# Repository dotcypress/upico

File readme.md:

## μPico

### What is it?

uPico is a [RP2040](https://www.raspberrypi.com/products/rp2040/) powered expansion card designed to enhance the capabilities of [Clockwork's uConsole](https://www.clockworkpi.com/uconsole).

⚠️ Only R-01 and CM4 core are supported by control application.
Work in progress for A04/A06 core modules.

Second project name is `atto`, cause 10<sup>−6</sup> * 10<sup>-12</sup> = 10<sup>-18</sup> 🤓

### Features

* Internal Speakers Support
* Type-C (USB 2.0) port with programmable power switch and overcurrent protection
* 3.3V and 5V external power out with programmable switch and overcurrent protection
* RP2040 with extenal double-double PMOD compatible connector
* RP2040 controllable LED

## Resources

- [Schematics](docs/upico.pdf)
- [PCB Viewer](https://kicanvas.org/?github=https%3A%2F%2Fgithub.com%2Fdotcypress%2Fupico%2Fblob%2Fmain%2Fpcb%2Fupico.kicad_pcb)
- [Interactive BOM](https://htmlpreview.github.io/?https://github.com/dotcypress/upico/blob/main/docs/ibom.html)

### Control app installation

1. Download latest build from [Releases page](https://github.com/dotcypress/upico/releases)
2. Extract installer: `mkdir dist && tar -xzf upico_%version%.%core%.tar.gz -C dist`
3. Install: `cd dist && sudo ./install.sh`
4. Cleanup: `cd .. && rm -rf dist`
5. Print help: `upico help`

### Building control app from sources

1. Install rustup by following the instructions at https://rustup.rs
2. Clone this repo: `git clone git@github.com:dotcypress/upico.git && cd upico`
3. Build: `cargo build --release`
4. Install app: `sudo cp target/release/upico /usr/local/bin/`
5. Install service: `sudo cp upico.service /etc/systemd/system/`
6. Enable service: `sudo systemctl enable upico`
7. Start service: `sudo systemctl start upico`
8. Setup uPico extender USB device: `echo 'SUBSYSTEM=="usb",ATTRS{idVendor}=="1209",ATTRS{idProduct}=="bc07",MODE="0660",GROUP="plugdev"' > /etc/udev/rules.d/50-upico-permissions.rules`
9. Reload udev: `udevadm control --reload-rules`
10. Print help: `upico help`

### Flash firmware

1. `wget https://rptl.io/pico-blink`
2. `upico install pico-blink` or `upico install -m pico-blink` if automount is disabled for hot-plug devices.

See other examples: https://github.com/raspberrypi/pico-examples

### High level design diagram

### GPIO Header Pinout
```
╔══════╦══════╗
║ AUX  ║ AUX  ║
╠══════╬══════╣
║ VDD  ║ VDD  ║
║ GND  ║ GND  ║
║ IO3  ║ IO7  ║
║ IO2  ║ IO6  ║
║ IO1  ║ IO5  ║
║ IO0  ║ IO4  ║
╠══════╬══════╣
║ IO27 ║ IO29 ║
║ IO26 ║ IO28 ║
║ IO18 ║ IO19 ║
╠══════╬══════╣
║ VDD  ║ VDD  ║
║ GND  ║ GND  ║
║ IO11 ║ IO15 ║
║ IO10 ║ IO14 ║
║ IO9  ║ IO13 ║
║ IO8  ║ IO12 ║
╚══════╩══════╝
```

## Errata

### CM4 core & uPico PCB rev:0x02

* Overcurrent reporting feature isn't supported.

## License

Licensed under either of

- Apache License, Version 2.0 ([LICENSE-APACHE](LICENSE-APACHE) or
  http://www.apache.org/licenses/LICENSE-2.0)
- MIT license ([LICENSE-MIT](LICENSE-MIT) or http://opensource.org/licenses/MIT)

at your option.

### Contribution

Unless you explicitly state otherwise, any contribution intentionally submitted
for inclusion in the work by you, as defined in the Apache-2.0 license, shall be
dual licensed as above, without any additional terms or conditions.

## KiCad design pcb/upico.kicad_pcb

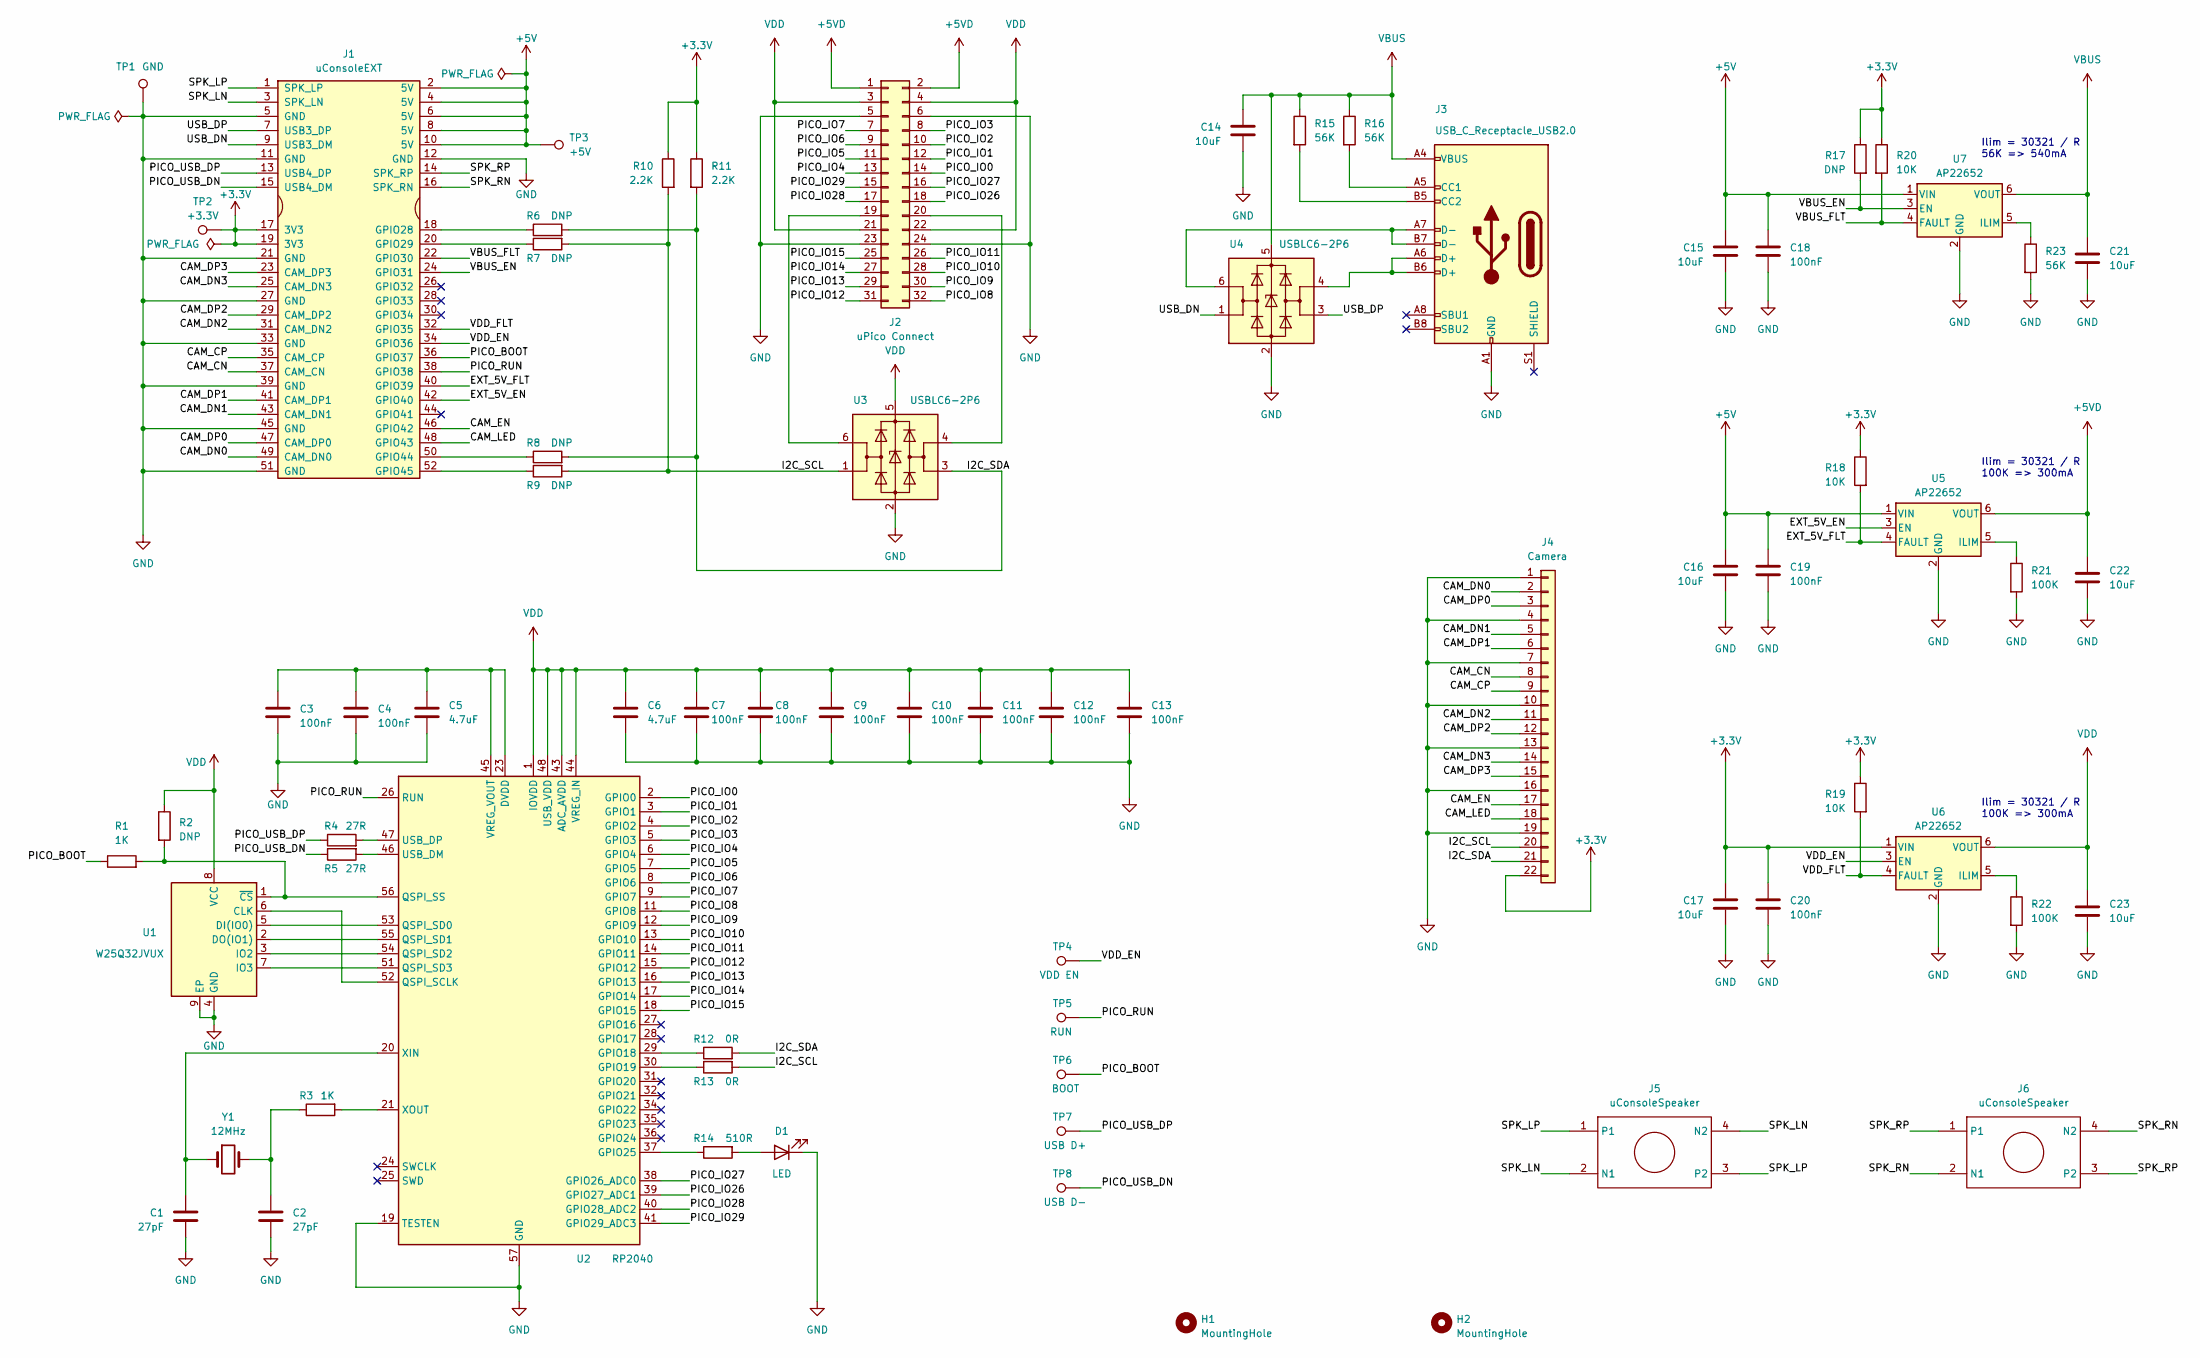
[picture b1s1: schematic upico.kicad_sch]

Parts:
C1, C2: 27pF; C_0402_1005Metric
C3, C4, C7, C8, C9, C10, C11, C12, C13, C18, C19, C20: 100nF; C_0402_1005Metric
C5, C6: 4.7uF; C_0402_1005Metric
C14, C15, C16, C17, C21, C22, C23: 10uF; C_0603_1608Metric
D1: LED; LED_SideEmitter_Rectangular_W4.5mm_H1.6mm
H1, H2: MountingHole; MountingHole_5.3mm_M5
J1: uConsoleEXT; ext
J2: uPico Connect; PinSocket_2x16_P2.54mm_Horizontal
J3: USB_C_Receptacle_USB2.0; USB_C_Receptacle_HRO_TYPE-C-31-M-12
J4: Camera; Hirose_FH12-22S-0.5SH_1x22-1MP_P0.50mm_Horizontal
J5, J6: uConsoleSpeaker; speaker
R1, R3: 1K; R_0402_1005Metric
R2, R6, R7, R8, R9, R17: DNP; R_0402_1005Metric
R4, R5: 27R; R_0402_1005Metric
R10, R11: 2.2K; R_0402_1005Metric
R12, R13: 0R; R_0402_1005Metric
R14: 510R; R_0402_1005Metric
R15, R16, R23: 56K; R_0402_1005Metric
R18, R19, R20: 10K; R_0402_1005Metric
R21, R22: 100K; R_0402_1005Metric
TP1: GND; TestPoint_Pad_D1.0mm
TP2: +3.3V; TestPoint_Pad_D1.0mm
TP3: +5V; TestPoint_Pad_D1.0mm
TP4: VDD EN; TestPoint_Pad_D1.0mm
TP5: RUN; TestPoint_Pad_D1.0mm
TP6: BOOT; TestPoint_Pad_D1.0mm
TP7: USB D+; TestPoint_Pad_D1.0mm
TP8: USB D-; TestPoint_Pad_D1.0mm
U1: W25Q32JVUX; USON-8_2x3mm_P0.5mm
U2: RP2040; QFN-56-1EP_7x7mm_P0.4mm_EP3.2x3.2mm
U3, U4: USBLC6-2P6; SOT-666
U5, U6, U7: AP22652; SOT-23-6
Y1: 12MHz; Crystal_SMD_5032-2Pin_5.0x3.2mm

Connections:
+3.3V: C17.2, C20.2, J1.17 (3V3), J1.19 (3V3), J4.22, R10.1, R11.1, R17.1, R18.1, R19.1, R20.1, TP2.1, U6.1 (VIN)
+5V: C15.2, C16.2, C18.2, C19.2, J1.2 (5V), J1.4 (5V), J1.6 (5V), J1.8 (5V), J1.10 (5V), TP3.1, U5.1 (VIN), U7.1 (VIN)
+5VD: C22.1, J2.1, J2.2, U5.6 (VOUT)
/CAM_CN: J1.37 (CAM_CN), J4.8
/CAM_CP: J1.35 (CAM_CP), J4.9
/CAM_DN0: J1.49 (CAM_DN0), J4.2
/CAM_DN1: J1.43 (CAM_DN1), J4.5
/CAM_DN2: J1.31 (CAM_DN2), J4.11
/CAM_DN3: J1.25 (CAM_DN3), J4.14
/CAM_DP0: J1.47 (CAM_DP0), J4.3
/CAM_DP1: J1.41 (CAM_DP1), J4.6
/CAM_DP2: J1.29 (CAM_DP2), J4.12
/CAM_DP3: J1.23 (CAM_DP3), J4.15
/CAM_EN: J1.46 (GPIO42), J4.17
/CAM_LED: J1.48 (GPIO43), J4.18
/EXT_5V_EN: J1.42 (GPIO40), U5.3 (EN)
/EXT_5V_FLT: J1.40 (GPIO39), R18.2, U5.4 (FAULT)
/I2C_SCL: J4.20, R7.2, R9.2, R10.2, R13.2, U3.1 (I/O1)
/I2C_SDA: J4.21, R6.2, R8.2, R11.2, R12.2, U3.3 (I/O2)
/PICO_BOOT: J1.36 (GPIO37), R1.1, TP6.1
/PICO_IO0: J2.14, U2.2 (GPIO0)
/PICO_IO1: J2.12, U2.3 (GPIO1)
/PICO_IO2: J2.10, U2.4 (GPIO2)
/PICO_IO3: J2.8, U2.5 (GPIO3)
/PICO_IO4: J2.13, U2.6 (GPIO4)
/PICO_IO5: J2.11, U2.7 (GPIO5)
/PICO_IO6: J2.9, U2.8 (GPIO6)
/PICO_IO7: J2.7, U2.9 (GPIO7)
/PICO_IO8: J2.32, U2.11 (GPIO8)
/PICO_IO9: J2.30, U2.12 (GPIO9)
/PICO_IO10: J2.28, U2.13 (GPIO10)
/PICO_IO11: J2.26, U2.14 (GPIO11)
/PICO_IO12: J2.31, U2.15 (GPIO12)
/PICO_IO13: J2.29, U2.16 (GPIO13)
/PICO_IO14: J2.27, U2.17 (GPIO14)
/PICO_IO15: J2.25, U2.18 (GPIO15)
/PICO_IO26: J2.18, U2.39 (GPIO27_ADC1)
/PICO_IO27: J2.16, U2.38 (GPIO26_ADC0)
/PICO_IO28: J2.17, U2.40 (GPIO28_ADC2)
/PICO_IO29: J2.15, U2.41 (GPIO29_ADC3)
/PICO_RUN: J1.38 (GPIO38), TP5.1, U2.26 (RUN)
/PICO_USB_DN: J1.15 (USB4_DM), R5.1, TP8.1
/PICO_USB_DP: J1.13 (USB4_DP), R4.1, TP7.1
/SPK_LN: J1.3 (SPK_LN), J5.2 (N1), J5.4 (N2)
/SPK_LP: J1.1 (SPK_LP), J5.1, J5.3 (P2)
/SPK_RN: J1.16 (SPK_RN), J6.2 (N1), J6.4 (N2)
/SPK_RP: J1.14 (SPK_RP), J6.1, J6.3 (P2)
/USB_DN: J1.9 (USB3_DM), U4.1 (I/O1)
/USB_DP: J1.7 (USB3_DP), U4.3 (I/O2)
/VBUS_EN: J1.24 (GPIO31), R17.2, U7.3 (EN)
/VBUS_FLT: J1.22 (GPIO30), R20.2, U7.4 (FAULT)
/VDD_EN: J1.34 (GPIO36), TP4.1, U6.3 (EN)
/VDD_FLT: J1.32 (GPIO35), R19.2, U6.4 (FAULT)
GND: C1.2, C2.2, C3.2, C4.2, C5.2, C6.2, C7.2, C8.2, C9.2, C10.2, C11.2, C12.2, C13.2, C14.1, C15.1, C16.1, C17.1, C18.1, C19.1, C20.1, C21.2, C22.2, C23.2, D1.1 (K), J1.5 (GND), J1.11 (GND), J1.12 (GND), J1.21 (GND), J1.27 (GND), J1.33 (GND), J1.39 (GND), J1.45 (GND), J1.51 (GND), J2.5, J2.6, J2.23, J2.24, J3.A1 (GND), J3.A12 (GND), J3.B1 (GND), J3.B12 (GND), J4.1, J4.4, J4.7, J4.10, J4.13, J4.16, J4.19, R21.2, R22.2, R23.2, TP1.1, U1.4 (GND), U1.9 (EP), U2.19 (TESTEN), U2.57 (GND), U3.2 (GND), U4.2 (GND), U5.2 (GND), U6.2 (GND), U7.2 (GND)
unnamed: C2.1, R3.1, Y1.2
unnamed: D1.2 (A), R14.2
unnamed: J1.18 (GPIO28), R6.1
unnamed: J1.20 (GPIO29), R7.1
unnamed: J1.50 (GPIO44), R8.1
unnamed: J1.52 (GPIO45), R9.1
unnamed: J2.19, U3.6 (I/O1)
unnamed: J2.20, U3.4 (I/O2)
unnamed: J3.A5 (CC1), R16.2
unnamed: J3.B5 (CC2), R15.2
unnamed: J3.A6 (D+), J3.B6 (D+), U4.4 (I/O2)
unnamed: J3.A7 (D-), J3.B7 (D-), U4.6 (I/O1)
unnamed: U1.6 (CLK), U2.52 (QSPI_SCLK)
unnamed: U1.5 (DI(IO0)), U2.53 (QSPI_SD0)
unnamed: U1.2 (DO(IO1)), U2.55 (QSPI_SD1)
unnamed: U1.3 (IO2), U2.54 (QSPI_SD2)
unnamed: U1.7 (IO3), U2.51 (QSPI_SD3)
unnamed: R1.2, R2.2, U1.1 (~CS), U2.56 (QSPI_SS)
unnamed: R12.1, U2.29 (GPIO18)
unnamed: R13.1, U2.30 (GPIO19)
unnamed: R14.1, U2.37 (GPIO25)
unnamed: R5.2, U2.46 (USB_DM)
unnamed: R4.2, U2.47 (USB_DP)
unnamed: C3.1, C4.1, C5.1, U2.23 (DVDD), U2.45 (VREG_VOUT), U2.50 (DVDD)
unnamed: C1.1, U2.20 (XIN), Y1.1
unnamed: R3.2, U2.21 (XOUT)
unnamed: R21.1, U5.5 (ILIM)
unnamed: R22.1, U6.5 (ILIM)
unnamed: R23.1, U7.5 (ILIM)
VBUS: C14.2, C21.1, J3.A4 (VBUS), J3.A9 (VBUS), J3.B4 (VBUS), J3.B9 (VBUS), R15.1, R16.1, U4.5 (VBUS), U7.6 (VOUT)
VDD: C6.1, C7.1, C8.1, C9.1, C10.1, C11.1, C12.1, C13.1, C23.1, J2.3, J2.4, J2.21, J2.22, R2.1, U1.8 (VCC), U2.1 (IOVDD), U2.10 (IOVDD), U2.22 (IOVDD), U2.33 (IOVDD), U2.42 (IOVDD), U2.43 (ADC_AVDD), U2.44 (VREG_IN), U2.48 (USB_VDD), U2.49 (IOVDD), U3.5 (VBUS), U6.6 (VOUT)

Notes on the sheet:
Ilim = 30321 / R 56K => 540mA
Ilim = 30321 / R 100K => 300mA

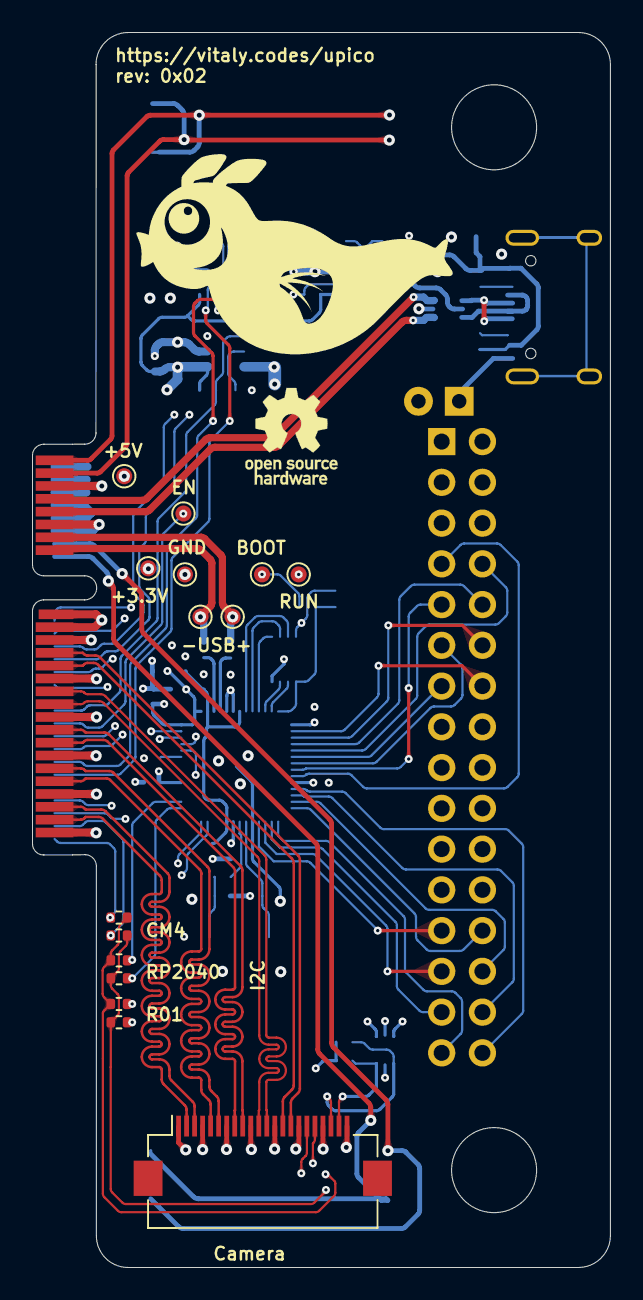
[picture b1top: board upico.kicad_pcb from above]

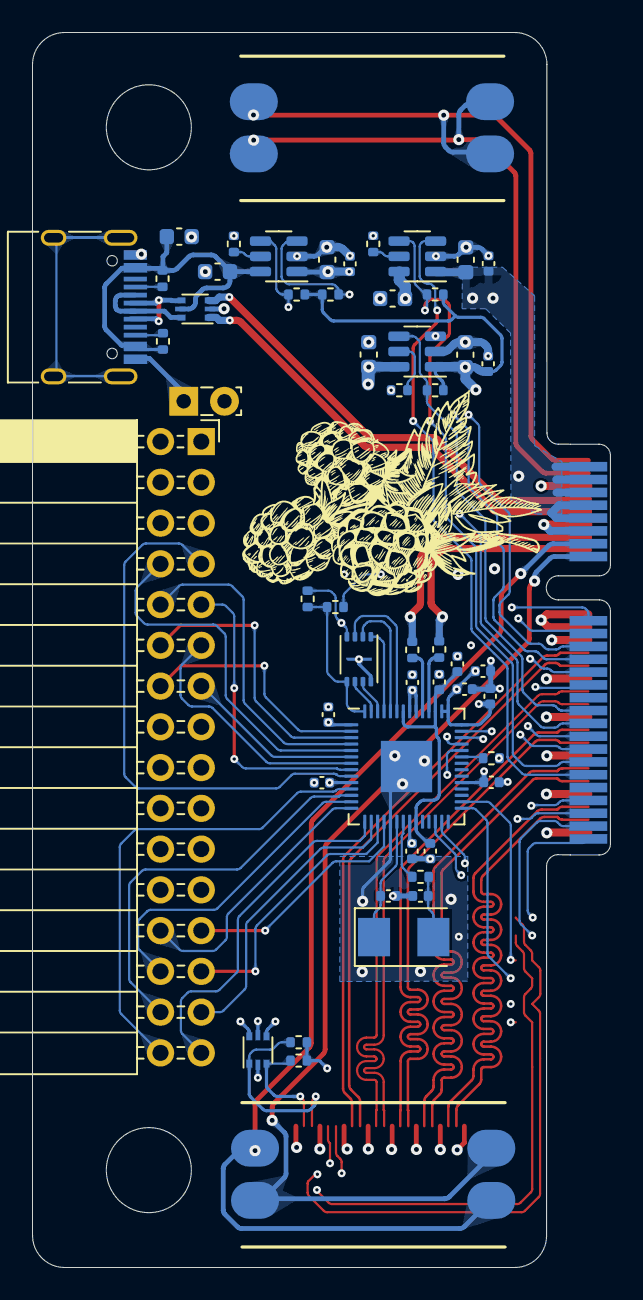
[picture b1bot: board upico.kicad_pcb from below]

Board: 6 copper layers, 36.0 x 77.0 mm, 71 parts (53 on the bottom side), 85 nets.

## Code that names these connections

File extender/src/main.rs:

#![no_std]
#![no_main]

extern crate panic_probe;
extern crate rp2040_hal as hal;
extern crate rtic;

use defmt_rtt as _;

mod upico;

use cortex_m::singleton;
use hal::adc;
use hal::gpio::*;
use hal::pac;
use hal::pio::{PIOBuilder, PIOExt};
use hal::timer::{monotonic::Monotonic, *};
use hal::usb::UsbBus;
use pio::Assembler;
use upico::*;
use usb_device::class_prelude::*;
use usb_device::prelude::*;

#[link_section = ".boot2"]
#[no_mangle]
#[used]
pub static BOOT2: [u8; 256] = rp2040_boot2::BOOT_LOADER_GENERIC_03H;

pub const XTAL_FREQ_HZ: u32 = 12_000_000_u32;

#[rtic::app(device = pac, peripherals = true, dispatchers = [SW0_IRQ, SW1_IRQ])]
mod app {
    use super::*;

    #[monotonic(binds = TIMER_IRQ_0, default = true)]
    type Oracle = Monotonic<Alarm0>;

    #[local]
    struct Local {
        upico: UpicoClass,
        usb_dev: UsbDevice<'static, hal::usb::UsbBus>,
    }

    #[shared]
    struct Shared {}

    #[init]
    fn init(ctx: init::Context) -> (Shared, Local, init::Monotonics) {
        let mut resets = ctx.device.RESETS;
        let mut watchdog = hal::Watchdog::new(ctx.device.WATCHDOG);
        let clocks = hal::clocks::init_clocks_and_plls(
            XTAL_FREQ_HZ,
            ctx.device.XOSC,
            ctx.device.CLOCKS,
            ctx.device.PLL_SYS,
            ctx.device.PLL_USB,
            &mut resets,
            &mut watchdog,
        )
        .ok()
        .expect("Clocks init failed");

        let mut timer = hal::Timer::new(ctx.device.TIMER, &mut resets, &clocks);
        let alarm = timer.alarm_0().expect("Alarm0 init failed");
        let mono = Monotonic::new(timer, alarm);

        let sio = hal::Sio::new(ctx.device.SIO);
        let pins = Pins::new(
            ctx.device.IO_BANK0,
            ctx.device.PADS_BANK0,
            sio.gpio_bank0,
            &mut resets,
        );
        let led = pins.gpio25.into_push_pull_output();
        let adc = adc::Adc::new(ctx.device.ADC, &mut resets);
        let adc_pins = (
            adc::AdcPin::new(pins.gpio26),
            adc::AdcPin::new(pins.gpio27),
            adc::AdcPin::new(pins.gpio28),
            adc::AdcPin::new(pins.gpio29),
        );

        pins.gpio0.into_function::<FunctionPio0>();
        pins.gpio1.into_function::<FunctionPio0>();
        pins.gpio2.into_function::<FunctionPio0>();
        pins.gpio3.into_function::<FunctionPio0>();
        pins.gpio4.into_function::<FunctionPio0>();
        pins.gpio5.into_function::<FunctionPio0>();
        pins.gpio6.into_function::<FunctionPio0>();
        pins.gpio7.into_function::<FunctionPio0>();
        pins.gpio8.into_function::<FunctionPio0>();
        pins.gpio9.into_function::<FunctionPio0>();
        pins.gpio10.into_function::<FunctionPio0>();
        pins.gpio11.into_function::<FunctionPio0>();
        pins.gpio12.into_function::<FunctionPio0>();
        pins.gpio13.into_function::<FunctionPio0>();
        pins.gpio14.into_function::<FunctionPio0>();
        pins.gpio15.into_function::<FunctionPio0>();

        let mut asm = Assembler::new();
        let mut wrap_target = asm.label();
        let mut wrap_source = asm.label();
        asm.bind(&mut wrap_target);
        asm.out(pio::OutDestination::EXEC, 32);
        asm.bind(&mut wrap_source);
        let (mut pio, sm, _, _, _) = ctx.device.PIO0.split(&mut resets);
        let program = pio.install(&asm.assemble_program()).unwrap();
        let (sm, rx, tx) = PIOBuilder::from_program(program)
            .autopull(true)
            .autopush(true)
            .pull_threshold(32)
            .push_threshold(32)
            .in_pin_base(0)
            .out_pins(0, 16)
            .build(sm);
        sm.start();

        let usb_regs = ctx.device.USBCTRL_REGS;
        let usb_dpram = ctx.device.USBCTRL_DPRAM;
        let usb_bus = UsbBus::new(usb_regs, usb_dpram, clocks.usb_clock, true, &mut resets);
        let usb_bus: &'static UsbBusAllocator<UsbBus> =
            singleton!(: UsbBusAllocator<UsbBus> = UsbBusAllocator::new(usb_bus))
                .expect("USB init failed");

        let upico = UpicoClass::new(usb_bus, rx, tx, adc, adc_pins, led);
        let usb_dev = UsbDeviceBuilder::new(usb_bus, UsbVidPid(0x1209, 0xbc07))
            .manufacturer("vitaly.codes")
            .product("uPico GPIO Extender")
            .build();
        unsafe {
            pac::NVIC::unmask(pac::Interrupt::USBCTRL_IRQ);
        };

        (Shared {}, Local { upico, usb_dev }, init::Monotonics(mono))
    }

    #[task(binds = USBCTRL_IRQ, local = [usb_dev, upico])]
    fn usb_irq(ctx: usb_irq::Context) {
        ctx.local.usb_dev.poll(&mut [ctx.local.upico]);
    }
}

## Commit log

2023-07-31 proto
2023-07-31 speakers
2023-08-06 basics
2023-08-13 aux routing
2023-08-13 power routing
2023-10-07 control app
2023-10-10 add BOM
2023-10-11 control app refactoring
2023-10-11 update cover
2023-10-12 change USB connector
2023-10-13 update control app
2023-10-14 update pcb
2023-10-14 code cleanup
2023-10-14 fix typo
2023-10-14 add pinout diagram
2023-10-14 enable vdd before entering bootloader
2023-10-14 MATH!
2023-10-15 add oshwa certification
2023-10-18 use features for core selection
2023-10-18 update gh actions script
2023-10-18 update project structure
2023-10-18 update ci script
2023-10-18 switch from gpiocdev to wiring pi
2023-10-18 add tindie banner
2023-10-25 invert power control signals
2023-10-28 update github actions
2023-10-28 installer script
2023-10-28 update docs
2023-11-01 pico auto mount
2023-11-01 0.0.1
2023-11-23 update CM4 pins
2023-11-23 update CM4 build config
2023-11-23 update installer
2023-11-23 cm4 port
2023-11-23 add cm4 & r-01 platform config
2023-11-23 0.1.0
2023-11-23 pico disc auto discovery
2023-11-24 core module feature
2023-11-24 A06 build
2023-11-24 update A06 pins
2023-11-25 update gpio
2024-04-14 gpio extender
2024-04-15 extender led
2024-04-15 updat default feature
2024-04-15 gpio set bugfix
2024-04-17 shell completions
2024-04-29 0.2.0
2024-05-09 generalize mount path
2024-06-22 bookworm linux support
2024-06-22 0.2.1
